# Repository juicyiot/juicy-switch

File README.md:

# Juicy Switch :electric_plug::tangerine:

A **RESTful** power **switch**.
The Juicy Switch enables you to turn a 230VAC device **on** and **off** using **HTTP**. E.g. you can switch a :bulb: on by calling `http://juicy.local/on`
and turn it off with `http://juicy.local/off`.

## :warning: Disclaimer :zap:
Mains can kill or severly injure people! Please read about electrical saftey first.
We designed the PCB to the best of our knowledge to be safe (see [Safety](hardware/README.md#safety) and [Enclosure](hardware/Readme.md#enclosure)), however **use it at your own risk**, we are no electrical engineers!

## Design goals
- DIY (do it yourself) :hammer:
- Affordable :dollar:
- Easy to setup and to use (your mom can use it :wink:)
- Simple yet powerful :rocket:

The Juicy Switch can be self assembled and is affordable, see [Bill of Materials](hardware/README.md#bill-of-materials). The setup is a friction less and quick process. After the device is powered up, it will create a WIFI hotspot called `juicy_switch`. Connect with your Smartphone/Notebook and proceed with the one time [Setup](firmware/README.md#usage). Eventhough the switch is very simple to use, many *smart* use cases can be built on top, see [Use Case Ideas](#use-case-ideas) to get inspired.

## Hardware
Head over to the dedicated [Hardware-Readme](hardware/README.md#setup)

## Software
Head over to the dedicated [Firmaware-Readme](firmware/README.md#setup)

## Progress/Status
October 2017: PCB got produced and has been shipped.
January 2018: PCB soldered but found an issue

## Use Case Ideas
- Calendar
- IFTTT
- Google Home

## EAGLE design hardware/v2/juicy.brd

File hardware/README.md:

# Juicy Switch Hardware :electric_plug::tangerine:

## :warning: Disclaimer :zap:
Mains can kill or severly injure people! Please read about electrical saftey first.
We designed the PCB to the best of our knowledge to be safe (see [Safety](#safety) and [Enclosure](#enclosure)), however **use it at your own risk**, we are no electrical engineers!

## Hardware

### Bill of Materials

The cost per unit is roughly 10$.

| Marking    | Item             | Package           | Value         |
------------ | ---------------- |------------------ | ------------- |
|            | µC-ESP826 ESP-07 | -                 | -             |
|            | HLK-PM01         | -                 | -             |
| R1,R2,R6,R8| resistor         | SMD 0815          | 10kΩ          |
| R3,R4      | resistor         | SMD 0815          | 1kΩ           |
| R5         | resistor         | SMD 0815          | 120Ω          |
| R7         | varistor         | THT               | 250VAC/2500A  |
| C1         | capacitor        | SMD 0815          | 22µF          |
| C2,C4      | capacitor        | SMD 0815          | 10µF          |
| C3         | capacitor        | SMD               | 100µF         |
| C5,C6      | capactior        | SMD 0815          | 100nF         |
| J3,J5      | screw terminal   | THT               | 5m            |
| D1,D3      | LED              | THT               | 3mm           |
| D2         | diode 1n4148     | THT               | 200mA/100V/1V |
| F1         | fuse (slow blow) | glass tube 5x20mm | 0.3A          |
| F2         | fuse (fast blow) | glass tube 5x20mm | 6.3A          |
| F1,F2      | fuse holder      | THT 5x20mm        | -             |
| Q1         | transistor npn   | SMD SOT23-3       | 0.5A/40V      |
| K1         | relay            | -                 | 10A/250VAC    |
| U1         | voltage regulator| SOT23-3           | 3.3V          |
| S1         | tactile switch   | SMD (4x4x1.5mm)   | -             |
| J1,J2,J4,J6 | Headers         | THT               | -             |

#### Schematic

#### Board
Seeedstudio manufactured our board (2 layer and 1oz of copper).

### Assembly
- Solder the ESP and related resistors/capcitors.
- Flash the ESP with a bootloader, upload our sketch and verify it is correctly running.
- Solder the power supply and the related fuse/varistor.
- Solder the relay and related fuse.

### Enclosure
The PCB **must** be enclosed by a **plastic** box. Use **non conducting** materials, e.g. plastic standoffs. The box should be kept in a dry environment (inside). Do not open the box while connected to mains, always unplug first.

### Sources
- https://esp8266.github.io/Arduino/versions/2.3.0/doc/boards.html
- http://www.learnabout-electronics.org/PSU/psu10.php
- http://circuitcalculator.com/wordpress/2006/01/31/pcb-trace-width-calculator/
- http://lygte-info.dk/review/Power%20Mains%20to%205V%200.6A%20Hi-Link%20HLK-PM01%20UK.html
- https://forum.mysensors.org/topic/1607/safe-in-wall-ac-to-dc-transformers
- http://www.reo.co.uk/files/safety_7_-_low_voltage_directive.pdf
- http://creepage.com/

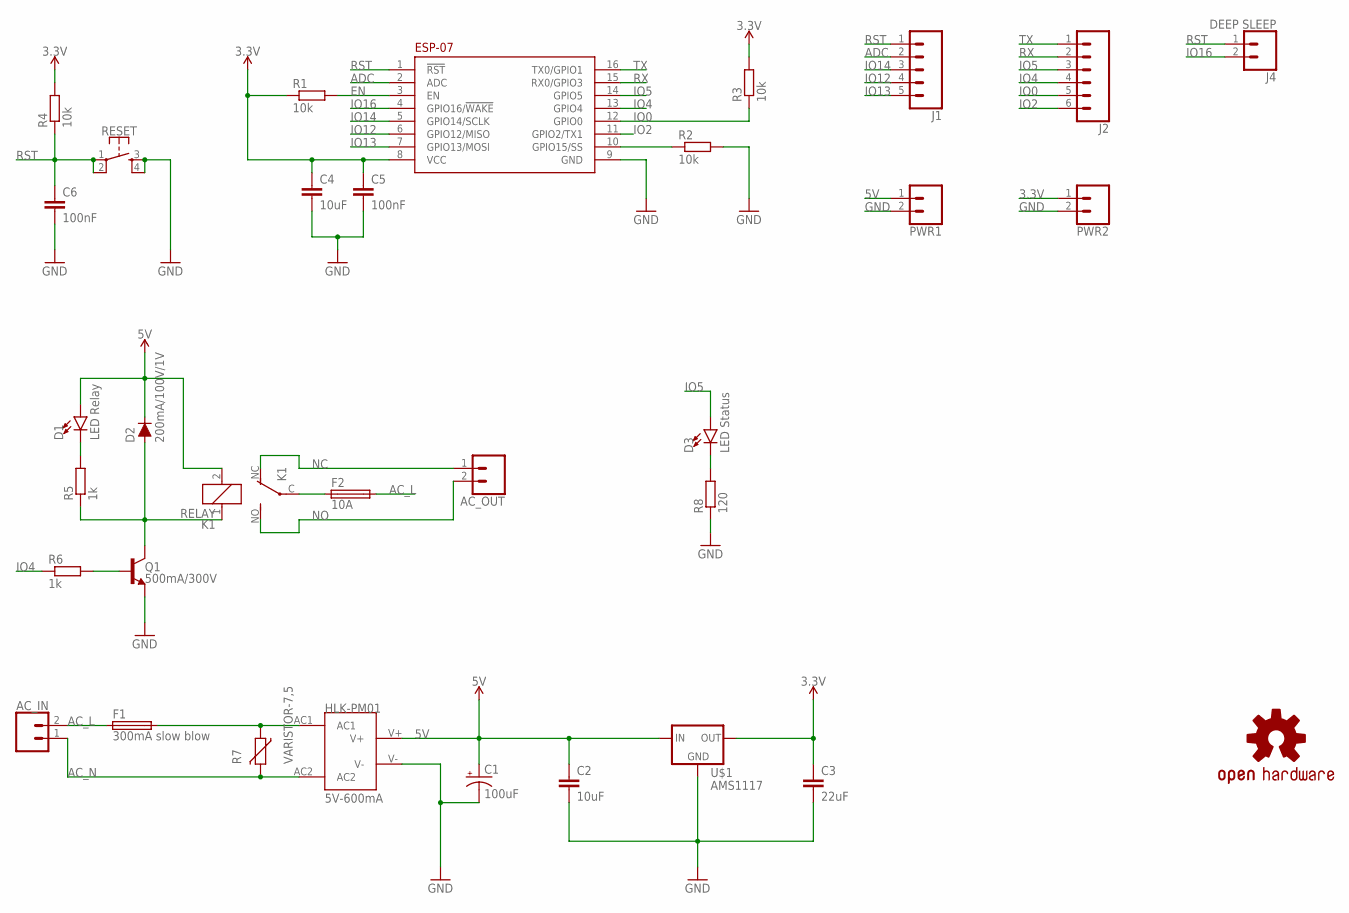
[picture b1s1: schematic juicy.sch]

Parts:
AC_IN: CONN_025MM; SCREWTERMINAL-5MM-2
AC_OUT: CONN_025MM; SCREWTERMINAL-5MM-2
C1: 100uF; PANASONIC_D
C2, C4: 10uF; 0805
C3: 22uF; 0805
C5, C6: 100nF; 0805
D1: LED Relay; LED_3MM
D2: 200mA/100V/1V; DIODE-1N4148
D3: LED Status; LED_3MM
F1: 300mA slow blow; SH22,5
F2: 10A; SH22,5
J1: CONN_05; 1X05
J2: CONN_06SILK_FEMALE_PTH; 1X06
J4: DEEP SLEEP; 1X02
K1: RELAY; JS-M
LOGO1: OSHW-LOGOM; OSHW-LOGO-M
PWR1, PWR2: CONN_02; 1X02
Q1: 500mA/300V; SOT23-3
R1, R2, R3, R4: 10k; R0805
R5, R6: 1k; R0805
R7: VARISTOR-7,5; R-7,5
R8: 120; R0805
RESET: MOMENTARY-SWITCH-SPST-2-SMD-5.2MM; TACTILE_SWITCH_SMD_5.2MM
U$1: AMS1117; SOT223
U$2: ESP8266
U$3: HILINK; HLK-PM01

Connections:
3.3V: C3.1, C4.1, C5.1, PWR2.1, R1.1, R3.2, R4.2, U$1.2 (OUT), U$1.4 (OUT), U$2.8 (VCC)
5V: C1.+, C2.1, D1.A, D2.C, K1.2, PWR1.1, U$1.3 (IN), U$3.V+
AC1: F1.2, R7.1, U$3.AC1
AC_L: AC_IN.2, F1.1, F2.2
AC_N: AC_IN.1, R7.2, U$3.AC2
ADC: J1.2, U$2.2 (ADC)
EN: R1.2, U$2.3 (EN)
GND: C1.-, C2.2, C3.2, C4.2, C5.2, C6.2, PWR1.2, PWR2.2, Q1.2 (E), R2.2, R8.1, RESET.3, RESET.4, U$1.1 (GND), U$2.9 (GND), U$3.V-
IO0: J2.5, R3.1, U$2.12 (GPIO0)
IO2: J2.6, U$2.11 (GPIO2/TX1)
IO4: J2.4, R6.1, U$2.13 (GPIO4)
IO5: D3.A, J2.3, U$2.14 (GPIO5)
IO12: J1.4, U$2.6 (GPIO12/MISO)
IO13: J1.5, U$2.7 (GPIO13/MOSI)
IO14: J1.3, U$2.5 (GPIO14/SCLK)
IO16: J4.2, U$2.4 (GPIO16/!WAKE!)
unnamed: F2.1, K1.C
unnamed: R2.1, U$2.10 (GPIO15/SS)
unnamed: D2.A, K1.1, Q1.3 (C), R5.1
unnamed: D3.K (C), R8.2
unnamed: D1.K (C), R5.2
unnamed: Q1.1 (B), R6.2
NC: AC_OUT.1, K1.NC (O)
NO: AC_OUT.2, K1.NO (S)
RST: C6.1, J1.1, J4.1, R4.1, RESET.1, RESET.2, U$2.1 (!RST!)
RX: J2.2, U$2.15 (RX0/GPIO3)
TX: J2.1, U$2.16 (TX0/GPIO1)

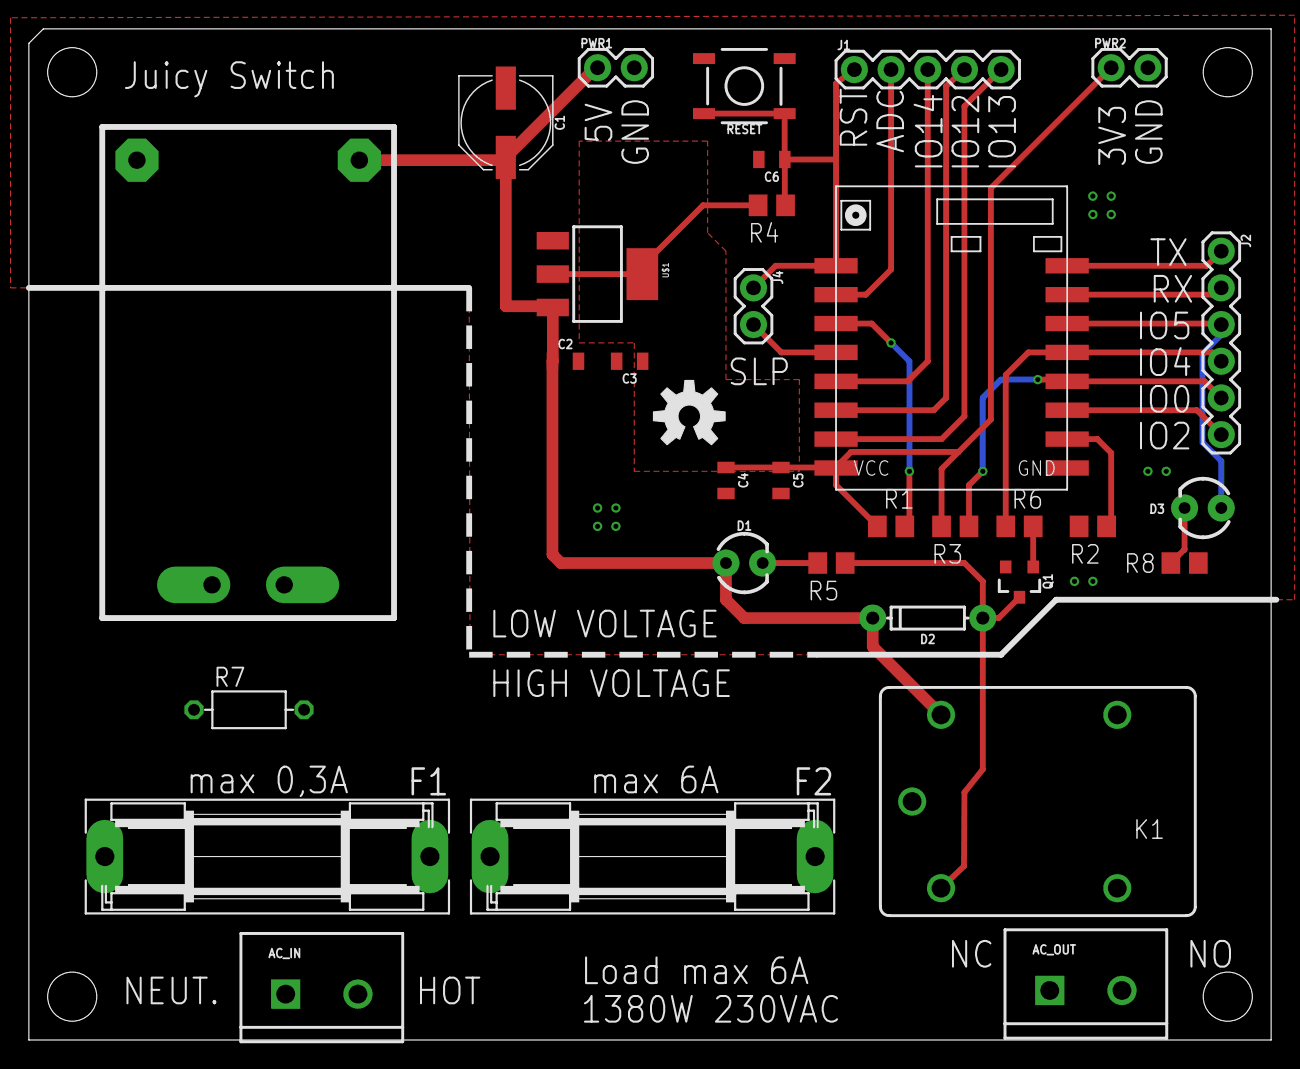
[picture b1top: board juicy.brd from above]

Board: 2 copper layers, 86.0 x 70.0 mm, 33 parts (0 on the bottom side), 27 nets.

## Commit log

2017-10-07 Add title to REAMDE
2017-10-07 Add clean platformio project
2017-10-07 Add WiFiScanner
2017-10-07 Remove destructor in WiFiScanner
2017-10-07 Add plain config server
2017-10-08 Setup captive portal
2017-10-08 Add empty config handlers
2017-10-08 Handle wifi scan in config server
2017-10-08 Remove logs
2017-10-08 Setup config handler
2017-10-08 Start save handler
2017-10-10 Refactor and clean up some things
2017-10-10 Setup credential storage
2017-10-10 Save network credentials in memory
2017-10-10 Setup connect trigger
2017-10-10 Connect to network with provided credentials
2017-10-10 Show connection status in config dialog
2017-10-10 Update disconnect
2017-10-11 Automatically connect using persistet credentials
2017-10-11 Change config server parameter names
2017-10-11 Add introduction to README
2017-10-11 Restructure config logic a bit
2017-10-11 Use enum over string for connection status
2017-10-11 Temporarily add API with wrong logic
2017-10-12 Add introduction to README (#1)
2017-10-18 Remove static done and add isDone()
2017-10-18 Revert "Remove static done and add isDone()"
    This reverts commit cd0a26dfc41bdfe22b7c65e6c5e3163a27d6b809.
2017-10-22 Add bill of materials and schematic/board
2017-10-22 Fix typo
2017-10-28 Add bill of materials and schematic/board (#2)
    * Add bill of materials and schematic/board
    * Fix typo
2017-10-28 Add connection class
2017-10-28 Disable captive portal
2017-10-29 Update and test API
2017-10-29 Add isSetup flag in API
2017-10-29 Refactor connection
2017-11-10 Add changes
2017-11-10 Refactor WiFiConnection
2017-11-10 Rename Connection to WiFiConnection
2017-11-10 Update connection
2017-11-10 Refactor API
2017-11-10 Refactor config server
2017-11-10 Further refactoring
2017-11-10 Add DNS server
2017-11-10 Add mdns service
2017-11-10 Persist credentials
2017-11-11 Remove old code and logs
2017-11-11 Fix wrong if statement
2017-11-11 Update HttpHandler
2017-11-11 Remove hostname from config and add it to API
2017-11-11 Add empty readme
2017-11-24 Remove autoreloading and refactor some things
2017-11-24 Make html mobile ready
2017-11-24 Add callbacks and clean up a bit
2017-11-24 Update feedback message for /save
2017-11-24 Remove debug clean on startup
2017-11-25 Refactor return statements
2017-11-25 Add first readme draft
2017-11-25 Add config flow image
2017-11-25 Add flow picture to readme
2017-11-25 Link nmap in readme
2017-11-25 Refactor API and add support for several pins
2017-12-05 Rename socket to switch
2017-12-05 Add exp07 env configuration
2017-12-05 Basic Firmware for WiFi Configuration and API (#3)
    * Add clean platformio project
    * Add WiFiScanner
    * Remove destructor in WiFiScanner
    * Add plain config server
    * Setup captive portal
    * Add empty config handlers
2017-12-06 Update travis config
2017-12-06 Move travis config to repo root
2017-12-06 Fix platformio.ini path in travis config
2017-12-06 Add build status badge to readmes
2017-12-06 Update build status badge to point to master
2017-12-07 Setup basic CI using Travis (#4)
    * Update travis config
    * Move travis config to repo root
    * Fix platformio.ini path in travis config
    * Add build status badge to readmes
    * Update build status badge to point to master
2018-03-26 Add hardware version 2
2018-03-26 Fix links
2018-03-26 Remove unused
2018-03-26 Add source files
2018-03-26 Adapt picture paths

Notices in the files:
parts and their libraries:
SparkFun-Connectors: Licensing: Creative Commons ShareAlike 4.0 International - https://creativecommons.org/licenses/by-sa/4.0
